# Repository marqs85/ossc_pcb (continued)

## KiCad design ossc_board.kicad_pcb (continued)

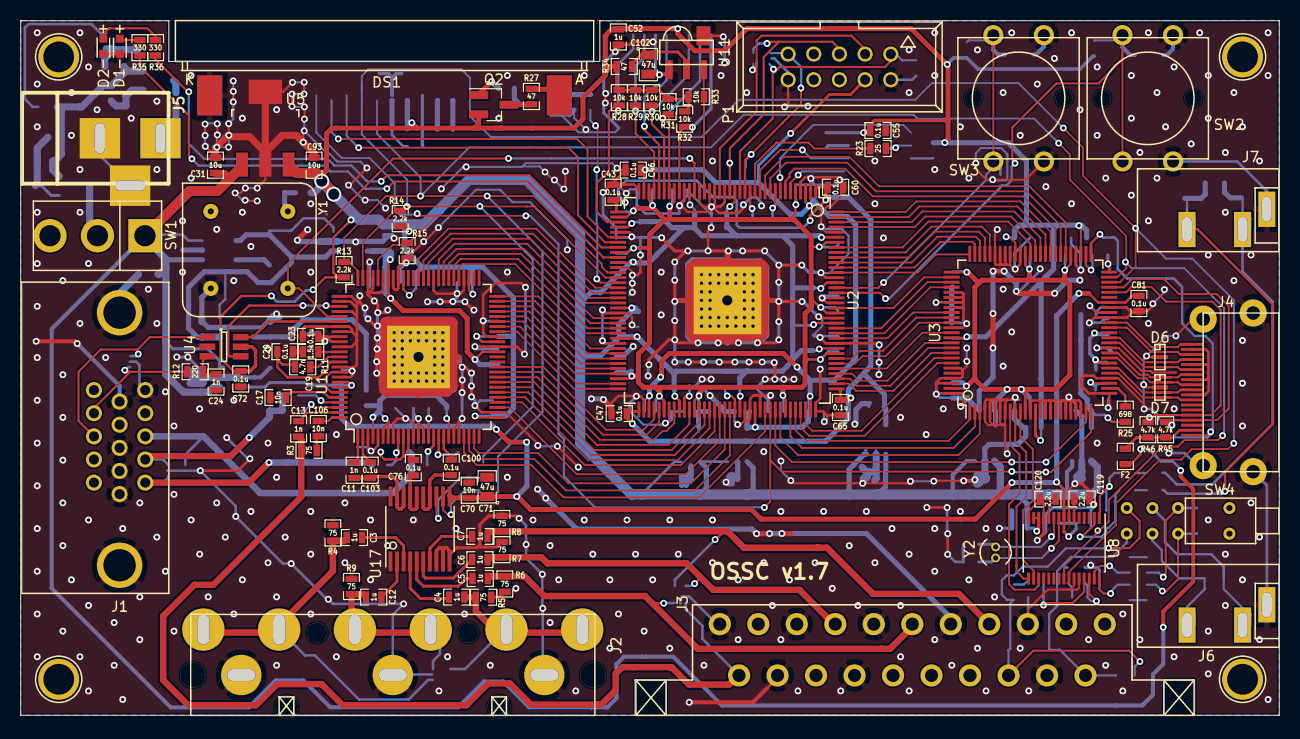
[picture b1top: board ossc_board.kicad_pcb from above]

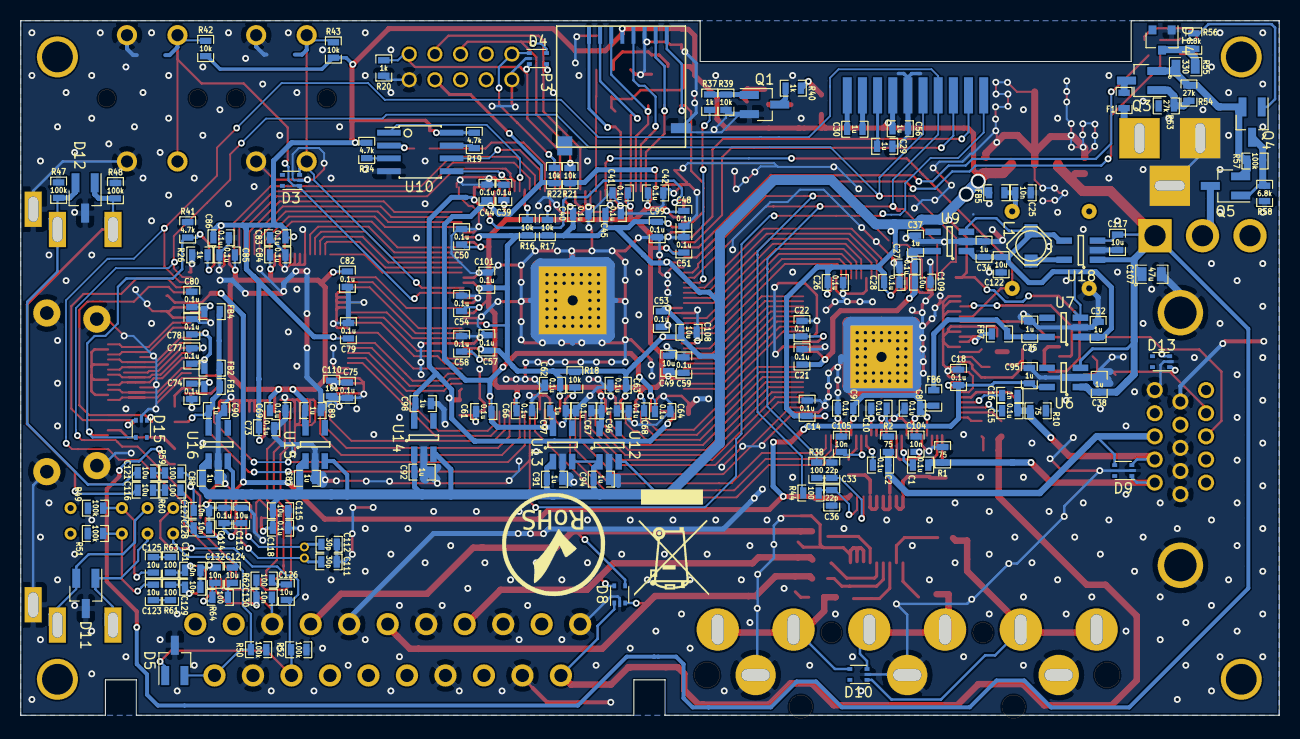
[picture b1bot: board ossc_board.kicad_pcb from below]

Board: 2 copper layers, 124.6 x 68.7 mm, 263 parts (171 on the bottom side), 211 nets.

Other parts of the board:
R59, R60, R61, R62, R63, R64: 100; SM0603_Resistor_libcms

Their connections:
unnamed 168: R60.2; also elsewhere on the board
unnamed 171: R59.1; also elsewhere on the board
unnamed 172: R61.2; also elsewhere on the board
unnamed 173: R64.2; also elsewhere on the board
unnamed 174: R63.2; also elsewhere on the board
unnamed 175: R62.2; also elsewhere on the board
unnamed 176: R59.2; also elsewhere on the board
unnamed 177: R60.1; also elsewhere on the board
unnamed 178: R61.1; also elsewhere on the board
unnamed 179: R62.1; also elsewhere on the board
unnamed 180: R63.1; also elsewhere on the board
unnamed 181: R64.1; also elsewhere on the board

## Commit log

2017-04-02 add pcb v1.6 (yet unfinished) design files
2017-04-14 finalize pcb v1.6
2017-04-14 v1.6-jp21
2017-06-25 Change R12 type.
2017-06-25 Add missing SMD position information.
2017-06-30 Add case files.
2017-07-01 Update BOM links.
2017-07-01 add case files
2017-07-01 OSH Park drill fixes
    When submitting the board to OSH Park (a popular hobbyist-friendly PCB
    fabrication service), two issues are present with the OSSC PCB:
    1. It contains plated slots (for the power and audio jacks, and the
    component video connector). These *are* supported by OSH Park, but
    lines must be added to the Edge.Cuts layer so that they are milled
    out properly. Otherwise, a hole will just be drilled at the start of
2017-07-03 Regenerate PCB files after recent small updates.
    - update R12 value on schematic, netlist and layout.
    - update ECS-3X9X footprint.
    - add pdf of the schematic.
2018-01-20 update BOM and instructions
2019-01-02 - Update schematics and board to KiCAD 5.x
2019-01-02 Add OpenboardView version for assembly support
2019-01-02 Update schematics PDF after upgrade
2019-01-02 Add 4mm print extrusions from SVG for 3D Printing
2019-01-07 fix pdf rotation and update BOM
2020-12-29 update to Kicad 5.x symbols
2021-07-22 fix D14 footprint and add RoHS & WEEE logos
2021-12-11 update case files and assembly instructions
2023-05-21 initial updates for pcb v1.8
    * update to new Kicad version
    * update schematic with SOGOUT connection
    * clean up layout
2023-07-26 additional updates for PCB v1.8
    * change to 4-layer stackup for better power delivery
    * choose another FPGA pin for PCB version indicator
2023-07-26 update to Kicad 7 and restore RoHS and WEEE logos
2023-08-01 change PCB version indicator pin due to conflict
2023-12-07 update iBOM
2024-01-12 regenerate schematic pdf
